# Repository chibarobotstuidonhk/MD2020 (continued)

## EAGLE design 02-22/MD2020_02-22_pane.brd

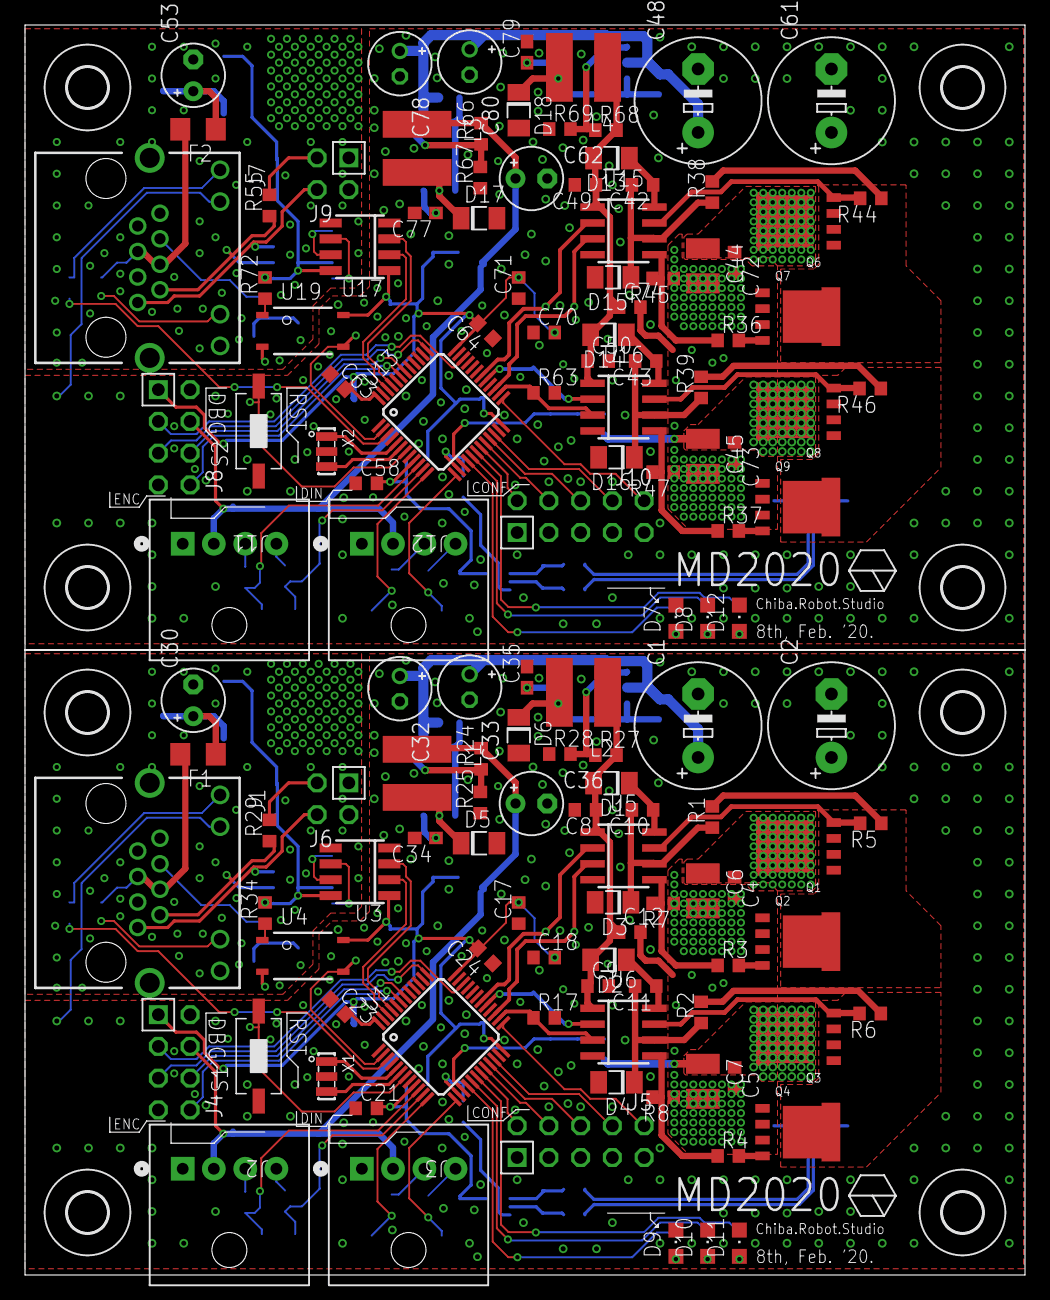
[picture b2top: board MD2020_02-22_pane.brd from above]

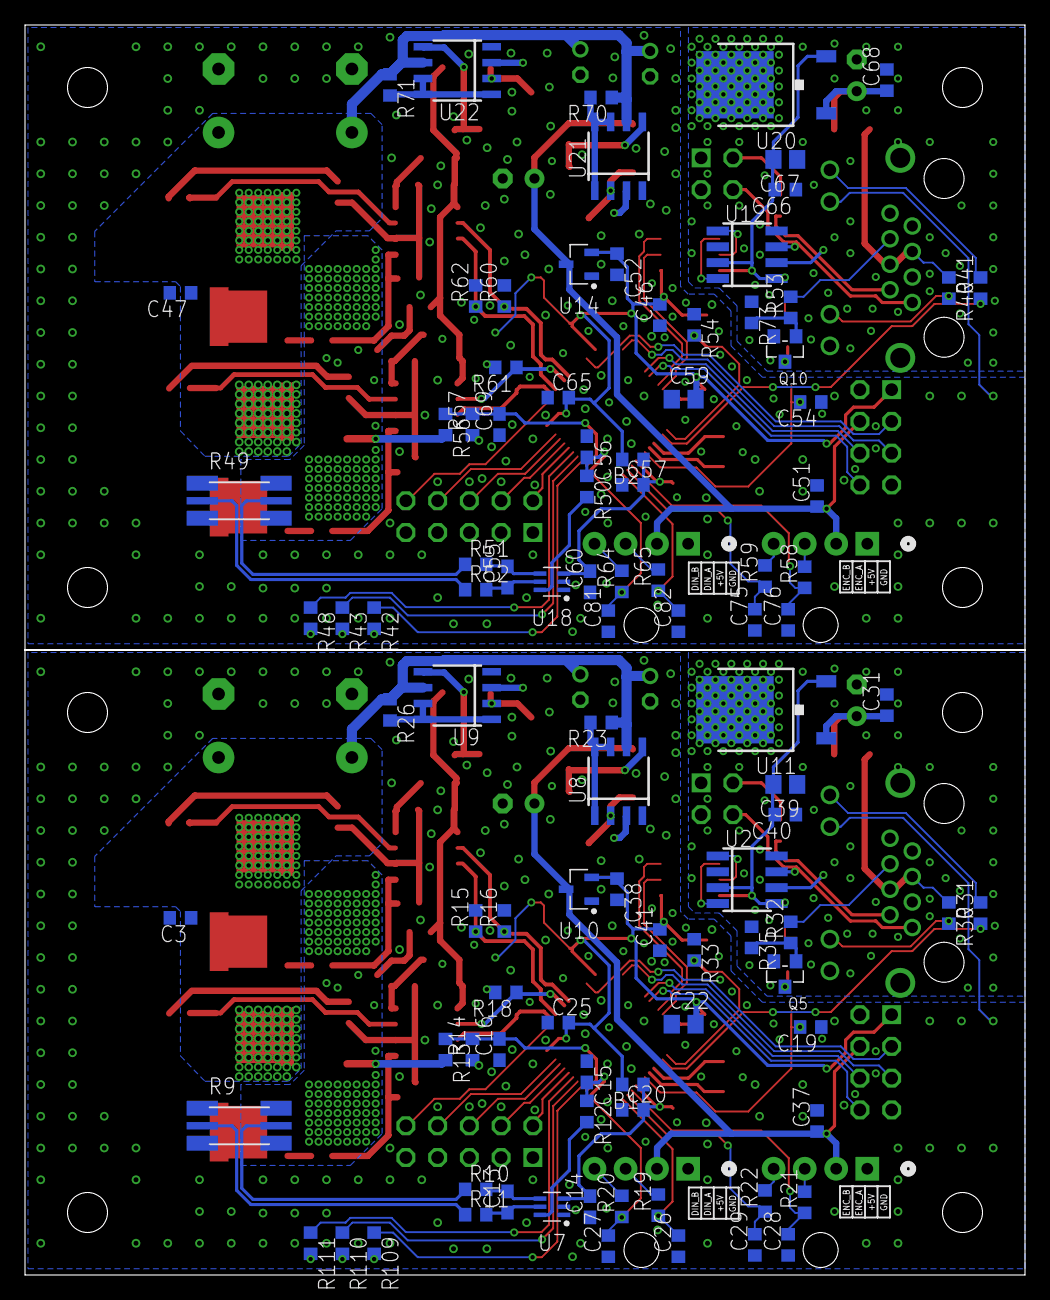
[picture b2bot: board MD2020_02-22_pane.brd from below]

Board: 2 copper layers, 80.0 x 100.0 mm, 240 parts (100 on the bottom side), 166 nets.

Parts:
B1, B2: FERRITE_BEAD; R0603
C1, C2, C48, C61: E5-10,5
C3, C4, C5, C9, C17, C18, C19, C23, C24, C25, C31, C37, C38, C40, C41, C46, C47, C50, C51, C52, C54, C63, C64, C65, C66, C68, C70, C71, C72, C73: 100n; C0603
C6, C7, C44, C45: 10u; C1210
C8, C12, C49, C74: 100n/50V; C0603
C10, C11, C42, C43: 100n/25V; C0603
C13, C14, C15, C16, C55, C56, C60, C69: C0603
C20, C57: 10n; C0603
C21, C58: 1u; C0603
C22, C59: 4u7; C0805
C26, C27, C28, C29, C34, C75, C76, C77, C81, C82: 220p; C0603
C30, C36, C53, C62: 22u; E2,5-5
C32, C33, C78, C80: 22u; E2-5
C35, C79: 330p; C0603
C39, C67: 10u; C0805
D1, D2, D3, D4, D5, D6, D13, D14, D15, D16, D17, D18: BAS70SOD-123F; SOD123F
D7, D8, D9, D10, D11, D12: CHIPLED_0805
F1, F2: R1206
H1, H2, H3, H4, H5, H6, H7, H8: MOUNT-HOLE3.2; 3,2
J1, J7: 8P8C-LED
J2, J3, J11, J12: 1744426-4; CONN4_1744426-4
J4, J8: MA04-2; MA04-2W
J5, J10: MA05-2; MA05-2W
J6, J9: MA02-2; MA02-2W
L1, L2, L3, L4: L5852
Q1, Q2, Q3, Q4, Q6, Q7, Q8, Q9: N-MOSFET-; SOT669
Q5, Q10: 2N7002; SOT-23
R1, R2, R3, R4, R12, R13, R14, R36, R37, R38, R39, R50, R56, R57: 10; R0603
R5, R6, R7, R8, R15, R16, R17, R18, R27, R35, R42, R44, R45, R46, R47, R60, R61, R62, R63, R68, R73, R109: 10k; R0603
R9, R49: 0.5m; CSS2H-2512
R10, R11, R51, R52: R0603
R19, R20, R21, R22, R58, R59, R64, R65: 100R; R0603
R23, R26, R70, R71: 0.47R; R0603
R24, R66: 3.6k; R0603
R25, R67: 1.2k; R0603
R28, R32, R33, R34, R43, R48, R53, R54, R69, R72, R110, R111: 1k; R0603
R29, R55: 120; R0603
R30, R40: 4k7; R0603
R31, R41: 470; R0603
S1, S2: SWITCH_TACTILETOP; SWITCH_TACTILE_3X6
U1, U13: STM32F103C8; LQFP48
U2, U12: NCV7351D1E; SO08
U3, U17: SI8621AB-B-IS; SO08
U4, U19: TLP184; 11-4M1S
U5, U6, U15, U16: NCP5106D; SOIC127P600X175-8
U7, U18: NCS199; SOT65P210X110-6
U8, U9, U21, U22: MC34063AD; SOIC8
U10, U14: XC6206; SOT95P240X110-3
U11, U20: 7805DT; TO252
X1, X2: 8MHZ; X3-SMD-3.6X1.3X0.8MM

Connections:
3V3A: B1.1, C14.2, C20.2, C21.2, U1.9, U7.3
3V3A1: B2.1, C57.2, C58.2, C60.2, U13.9, U18.3
5V_ISO: C39.2, C40.2, R34.2, U2.3, U2.5, U3.8, U11.2
5V_ISO1: C66.2, C67.2, R72.2, U12.3, U12.5, U17.8, U20.2
24V_ISO: C30.+, C31.1, F1.1, U11.1
24V_ISO1: C53.+, C68.1, F2.1, U20.1
!EMS: R33.2, U1.2, U4.3
!EMS1: R54.2, U13.2, U19.3
!EMS_ISO: J1.6, R32.2
!EMS_ISO1: J7.6, R53.2
!RESET: C19.2, S1.P$2, U1.7
!RESET1: C54.2, S2.P$2, U13.7
+3V1: B2.2, C46.2, C52.1, C59.2, C63.2, C64.2, C65.2, C70.2, C71.2, J8.8, U13.24, U13.36, U13.48, U14.2, U17.1, U19.4
+3V3: B1.2, C17.2, C18.2, C22.2, C23.2, C24.2, C25.2, C38.1, C41.2, J4.8, U1.24, U1.36, U1.48, U3.1, U4.4, U10.2
+5V: C36.+, C37.1, J2.2, J3.2, J4.5, L1.P$2, R24.2, U10.3
+5V1: C51.1, C62.+, J8.5, J11.2, J12.2, L3.P$2, R66.2, U14.3
+15V: C8.1, C9.1, C12.1, D1.A, D2.A, L2.P$2, R27.2, U5.1, U6.1
+15V1: C49.1, C50.1, C74.1, D13.A, D14.A, L4.P$2, R68.2, U15.1, U16.1
A_OUT: Q1.1, Q1.2, Q1.3, Q2.5, R1.2, R5.1
A_OUT1: Q6.1, Q6.2, Q6.3, Q7.5, R38.2, R44.1
B_OUT: Q3.1, Q3.2, Q3.3, Q4.5, R2.2, R6.1
B_OUT1: Q8.1, Q8.2, Q8.3, Q9.5, R39.2, R46.1
CANH: J1.1, J6.1, U2.7
CANH1: J7.1, J9.1, U12.7
CANL: J1.2, R29.1, U2.6
CANL1: J7.2, R55.1, U12.6
CANRX: U1.45, U3.3
CANRX1: U13.45, U17.3
CANTX: U1.46, U3.2
CANTX1: U13.46, U17.2
ENC_A: C28.2, R21.1, U1.10
ENC_A1: C76.2, R58.1, U13.10
ENC_B: C29.2, R22.1, U1.11
ENC_B1: C75.2, R59.1, U13.11
GNDA: C1.-, C2.-, C3.2, C8.2, C9.2, C14.1, C15.1, C16.1, C17.1, C18.1, C19.1, C20.1, C21.1, C22.1, C23.1, C24.1, C25.1, C26.1, C27.1, C28.1, C29.1, C32.-, C33.-, C34.2, C35.2, C36.-, C37.2, C38.2, C41.1, D3.A, D4.A, D5.A, D6.A, D9.C, D10.C, D11.C, J1.YC, J2.1, J3.1, J4.2, J4.7, J5.2, J5.4, J5.6, J5.8, J5.10, R9.1$1, R9.1$2, R14.1, R15.2, R16.2, R17.2, R18.2, R25.1, R28.1, R33.1, S1.P$1, U1.8, U1.23, U1.35, U1.44, U1.47, U3.4, U5.4, U6.4, U7.1, U7.2, U8.4, U9.4, U10.1, X1.2
GNDA1: C46.1, C47.2, C48.-, C49.2, C50.2, C51.2, C52.2, C54.1, C56.1, C57.1, C58.1, C59.1, C60.1, C61.-, C62.-, C63.1, C64.1, C65.1, C69.1, C70.1, C71.1, C75.1, C76.1, C77.2, C78.-, C79.2, C80.-, C81.1, C82.1, D7.C, D8.C, D12.C, D15.A, D16.A, D17.A, D18.A, J7.YC, J8.2, J8.7, J10.2, J10.4, J10.6, J10.8, J10.10, J11.1, J12.1, R49.1$1, R49.1$2, R54.1, R57.1, R60.2, R61.2, R62.2, R63.2, R67.1, R69.1, S2.P$1, U13.8, U13.23, U13.35, U13.44, U13.47, U14.1, U15.4, U16.4, U17.4, U18.1, U18.2, U21.4, U22.4, X2.2
GNDIO: C30.-, C31.2, C39.1, C40.1, J1.3, J1.7, J1.8, J1.GC, J1.M1, J1.M2, J6.3, J6.4, Q5.2, R35.1, U2.2, U2.8, U3.5, U11.3
GNDIO1: C53.-, C66.1, C67.1, C68.2, J7.3, J7.7, J7.8, J7.GC, J7.M1, J7.M2, J9.3, J9.4, Q10.2, R73.1, U12.2, U12.8, U17.5, U20.3
IN_A: C26.2, R19.1, U1.12
IN_A1: C82.2, R65.1, U13.12
IN_B: C27.2, R20.1, U1.13
IN_B1: C81.2, R64.1, U13.13
IN_HI_A: R16.1, U1.30, U5.2
IN_HI_A1: R60.1, U13.30, U15.2
IN_HI_B: R18.1, U1.29, U6.2
IN_HI_B1: R61.1, U13.29, U16.2
IN_LO_A: R15.1, U1.27, U5.3
IN_LO_A1: R62.1, U13.27, U15.3
IN_LO_B: R17.1, U1.26, U6.3
IN_LO_B1: R63.1, U13.26, U16.3
ISENSE: C15.2, R12.1, U1.14
ISENSE1: C56.2, R50.1, U13.14
JMP0: J5.9, U1.19
JMP1: J5.7, U1.20
JMP2: J5.5, U1.21
JMP3: J5.3, U1.22
JMP4: J5.1, U1.25
JMP5: J10.9, U13.19
JMP6: J10.7, U13.20
JMP7: J10.5, U13.21
JMP8: J10.3, U13.22
JMP9: J10.1, U13.25
LED0: R109.1, U1.16
LED1: R110.1, U1.17
LED2: R111.1, U1.18
LED3: R48.1, U13.18
LED4: R42.1, U13.16
LED5: R43.1, U13.17
LED_CAN: R31.1, U1.3
LED_CAN1: R41.1, U13.3
unnamed: Q1.4, R5.2, U5.7
unnamed: Q3.4, R6.2, U6.7
unnamed: D10.A, R110.2
unnamed: C10.2, D3.C, R1.1, U5.6
unnamed: R4.1, R8.2, U6.5
unnamed: R12.2, U7.6
unnamed: D9.A, R109.2
unnamed: F1.2, J1.4, J1.5, R30.1
unnamed: J6.2, R29.2
unnamed: U1.6, X1.3
unnamed: R3.1, R7.2, U5.5
unnamed: J2.4, R22.2
unnamed: R23.2, U8.1, U8.7, U8.8
unnamed: D5.C, L1.P$1, U8.2
unnamed: J3.4, R20.2
unnamed: J2.3, R21.2
unnamed: J3.3, R19.2
unnamed: J1.GA, R30.2
unnamed: U1.5, X1.1
unnamed: J1.YA, R31.2
unnamed: D11.A, R111.2
unnamed: Q5.1, R32.1, R35.2
unnamed: U2.1, U3.7
unnamed: C34.1, U8.3
unnamed: C11.2, D4.C, R2.1, U6.6
unnamed: R24.1, R25.2, U8.5
unnamed: U2.4, U3.6
unnamed: R26.2, U9.1, U9.7, U9.8
unnamed: D6.C, L2.P$1, U9.2
unnamed: Q5.3, U4.2
unnamed: R34.1, U4.1
unnamed: C35.1, U9.3
unnamed: R27.1, R28.2, U9.5
unnamed: Q7.4, R36.2
unnamed: Q9.4, R37.2
unnamed: C13.2, R10.2, U7.4
unnamed: C13.1, R11.2, U7.5
unnamed: C43.1, D14.C, U16.8
unnamed: C42.1, D13.C, U15.8
unnamed: R37.1, R47.2, U16.5
unnamed: Q6.4, R44.2, U15.7
unnamed: Q8.4, R46.2, U16.7
unnamed: D8.A, R43.2
unnamed: D7.A, R42.2
unnamed: U13.6, X2.3
unnamed: U13.5, X2.1
unnamed: R36.1, R45.2, U15.5
unnamed: F2.2, J7.4, J7.5, R40.1
unnamed: D12.A, R48.2
unnamed: U12.1, U17.7
unnamed: U12.4, U17.6
unnamed: R50.2, U18.6
unnamed: J7.GA, R40.2
unnamed: J7.YA, R41.2
unnamed: C55.2, R51.2, U18.4
unnamed: C55.1, R52.2, U18.5
unnamed: J9.2, R55.2
unnamed: J12.4, R64.2
unnamed: J12.3, R65.2
unnamed: J11.4, R59.2
unnamed: Q2.4, R3.2
unnamed: J11.3, R58.2
unnamed: C42.2, D15.C, R38.1, U15.6
unnamed: Q4.4, R4.2
unnamed: C43.2, D16.C, R39.1, U16.6
unnamed: R70.2, U21.1, U21.7, U21.8
unnamed: C11.1, D2.C, U6.8
unnamed: D17.C, L3.P$1, U21.2
unnamed: C77.1, U21.3
unnamed: R66.1, R67.2, U21.5
unnamed: R71.2, U22.1, U22.7, U22.8
unnamed: D18.C, L4.P$1, U22.2
unnamed: C10.1, D1.C, U5.8
unnamed: C79.1, U22.3
unnamed: R68.1, R69.2, U22.5
unnamed: Q10.1, R53.1, R73.2
unnamed: Q10.3, U19.2
unnamed: R72.1, U19.1
SWCLK: J4.4, U1.37
SWCLK1: J8.4, U13.37
SWDIO: J4.6, U1.34
SWDIO1: J8.6, U13.34
UART_RX: J4.1, U1.43
UART_RX1: J8.1, U13.43
UART_TX: J4.3, U1.42
UART_TX1: J8.3, U13.42
VCC: C1.+, C2.+, C3.1, C4.1, C5.1, C6.1, C7.1, C32.+, C33.+, Q1.5, Q3.5, R13.2, R23.1, R26.1, U8.6, U9.6
VCC1: C44.1, C45.1, C47.1, C48.+, C61.+, C72.1, C73.1, C78.+, C80.+, Q6.5, Q8.5, R56.2, R70.1, R71.1, U21.6, U22.6
VCS: C4.2, C5.2, C6.2, C7.2, C12.2, Q2.1, Q2.2, Q2.3, Q4.1, Q4.2, Q4.3, R7.1, R8.1, R9.2$1, R9.2$2
VCS1: C44.2, C45.2, C72.2, C73.2, C74.2, Q7.1, Q7.2, Q7.3, Q9.1, Q9.2, Q9.3, R45.1, R47.1, R49.2$1, R49.2$2
VCS_B_N: R9.1S, R11.1
VCS_B_N1: R49.1S, R52.1
VCS_B_P: R9.2S, R10.1
VCS_B_P1: R49.2S, R51.1
VSENSE: C16.2, R13.1, R14.2, U1.15
VSENSE1: C69.2, R56.1, R57.2, U13.15

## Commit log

2020-02-17 とりあえず色々修正した
2020-02-24 少々修正
